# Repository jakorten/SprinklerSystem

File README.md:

# SprinklerSystem
Repository for valve controllers etc.

Here I publish updates to Python and Arduino scripts to create my / your own irrigation system.

## System parts
CinqueValvoleHAT is used to control a pump system.
TinyRelayModule is used to control a larger (230V) relay to switch of the main pump.
DueValvoleZeroBoard is used to control two valves and also features sensors.

## Progress and links

June 2019:
- CinqueValvoleHAT: 5x Valve/Tap Controller board (v1.0 / v1.1) (https://github.com/jakorten/SprinklerSystem/tree/master/CinqueValvoleHAT)
- DueValvoleZeroBoard: 2x Valve/Tap under development, uses a SAMD21 microcontroller and interfaces with a Raspberry Pi Zero (W).
- TinyRelayModule is only a solderboard version for now.

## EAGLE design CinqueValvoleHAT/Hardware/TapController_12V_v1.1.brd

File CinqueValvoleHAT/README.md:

# SprinklerSystem: CinqueValvoleHAT
Repository for valve controllers etc.

## About
Here I publish updates to Python and Arduino scripts to create my / your own irrigation system.

June 2019:
- 5x Tap Controller board (v1.0 / v1.1) (CinqueValvoleHAT)

The CinqueValvoleHAT is used to control up to 5 valves.
- Typical valves have DC motors
- They will switch of when the limit is reached (fully open or fully closed)
- The print was designed to control 12V valves

Other DC motors can also be controlled using this HAT.
We have tested the HAT for 12V and below.

Most parts can handle up to 50V but that is the maximum, of you would
want to control 48V you should change some parts:
- 0.1uF/50V
- 22uF/63V

We use a voltage divider in v1.1 for AOD417, for 12V that would not have been
necessary. The AOD417 protects against wrong polarity.

The input (suggested 5V - 12V) is not connected to the rest of the system only to the
DRV8871 drivers.

Each DRV8871 can handle up to 3.6A (but is limited to about 2A by the 30k resistors) and
has a maximum voltage of 50V (< 45V recommended). In case you want to use the HAT as is
for 48V motors we suggest you make sure your supply only divers 45V or less which should
be more than enough for ball valves. Note: We did not test this so use at your own risk.

We did try to run our 12V ball valves at 7V and although they move slower they will work
just fine.

We used the valves from:
https://nl.aliexpress.com/store/4032047?spm=a2g0o.detail.1000002.2.6d6b58daLNaQAn
(e.g. https://nl.aliexpress.com/item/32896353276.html?spm=a2g0s.9042311.0.0.32b34c4dLBPZam)

## Source
The source lets your Raspberry Pi control the valves via a PCA9685 IC

## Credits

Thanks @Adafruit for not only providing us with the basis idea and HAT layout (https://www.adafruit.com/product/2348).
Their hat works well but we found it got too hot inside the narrow enclosure we used.
Also thanks to @Adafruit for their suggestion to use DRV8871 drivers (they sell separate boards).

Note: we have designed the HAT and software to interoperate with homebridge. We use a second Raspberry Pi that
runs homebridge and will allow to set the valves remotely.

# ToDo: Work in progress
- We have created a HMI system for operation without homebridge
- We still need to integrate this functionality with the current source.
- Other parts of the system will be uploaded as we go.
- We hope to make the system available for purchase using Tindie.

Johan Korten<br>
June 2019

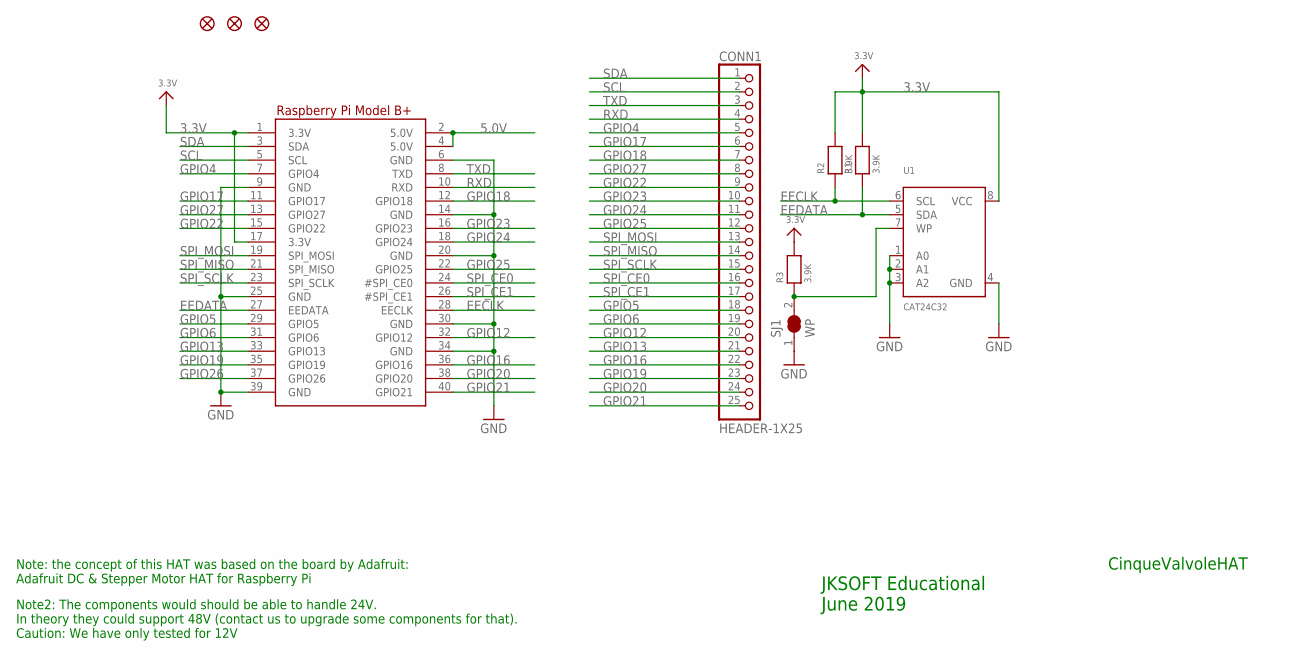
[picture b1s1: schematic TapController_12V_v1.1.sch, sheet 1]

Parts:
CONN1: HEADER-1X25; 1X25_ROUND_70MIL
FID1, FID2, FID3: FIDUCIAL""; FIDUCIAL_1MM
R1, R2, R3: 3.9K; 0805-NO@1
RPI1: RASPBERRYPI_BPLUS_HATSLOTS; PI_HAT_SLOTS
SJ1: WP; SOLDERJUMPER_CLOSEDWIRE
U1: CAT24C32; SOIC8_150MIL

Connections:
3.3V: R1.2, R2.2, R3.2, RPI1.1 (3.3V), RPI1.17 (3.3V), U1.8 (VCC); also elsewhere on the board
5.0V: RPI1.2 (5.0V), RPI1.4 (5.0V)
EECLK: R2.1, RPI1.28 (EECLK), U1.6 (SCL)
EEDATA: R1.1, RPI1.27 (EEDATA), U1.5 (SDA)
GND: RPI1.6 (GND), RPI1.9 (GND), RPI1.14 (GND), RPI1.20 (GND), RPI1.25 (GND), RPI1.30 (GND), RPI1.34 (GND), RPI1.39 (GND), SJ1.1, U1.1 (A0), U1.2 (A1), U1.3 (A2), U1.4 (GND); also elsewhere on the board
GPIO4: CONN1.5, RPI1.7 (GPIO4)
GPIO5: CONN1.18, RPI1.29 (GPIO5)
GPIO6: CONN1.19, RPI1.31 (GPIO6)
GPIO12: CONN1.20, RPI1.32 (GPIO12)
GPIO13: CONN1.21, RPI1.33 (GPIO13)
GPIO16: CONN1.22, RPI1.36 (GPIO16)
GPIO17: CONN1.6, RPI1.11 (GPIO17)
GPIO18: CONN1.7, RPI1.12 (GPIO18)
GPIO19: CONN1.23, RPI1.35 (GPIO19)
GPIO20: CONN1.24, RPI1.38 (GPIO20)
GPIO21: CONN1.25, RPI1.40 (GPIO21)
GPIO22: CONN1.9, RPI1.15 (GPIO22)
GPIO23: CONN1.10, RPI1.16 (GPIO23)
GPIO24: CONN1.11, RPI1.18 (GPIO24)
GPIO25: CONN1.12, RPI1.22 (GPIO25)
GPIO26: RPI1.37 (GPIO26)
GPIO27: CONN1.8, RPI1.13 (GPIO27)
unnamed: R3.1, SJ1.2, U1.7 (WP)
RXD: CONN1.4, RPI1.10 (RXD)
SCL: CONN1.2, RPI1.5 (SCL); also elsewhere on the board
SDA: CONN1.1, RPI1.3 (SDA); also elsewhere on the board
SPI_CE0: CONN1.16, RPI1.24 (#SPI_CE0)
SPI_CE1: CONN1.17, RPI1.26 (#SPI_CE1)
SPI_MISO: CONN1.14, RPI1.21 (SPI_MISO)
SPI_MOSI: CONN1.13, RPI1.19 (SPI_MOSI)
SPI_SCLK: CONN1.15, RPI1.23 (SPI_SCLK)
TXD: CONN1.3, RPI1.8 (TXD)

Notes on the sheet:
JKSOFT Educational June 2019
CinqueValvoleHAT
Note: the concept of this HAT was based on the board by Adafruit: Adafruit DC & Stepper Motor HAT for Raspberry Pi
Note2: The components would should be able to handle 24V. In theory they could support 48V (contact us to upgrade some components for that). Caution: We have only tested for 12V

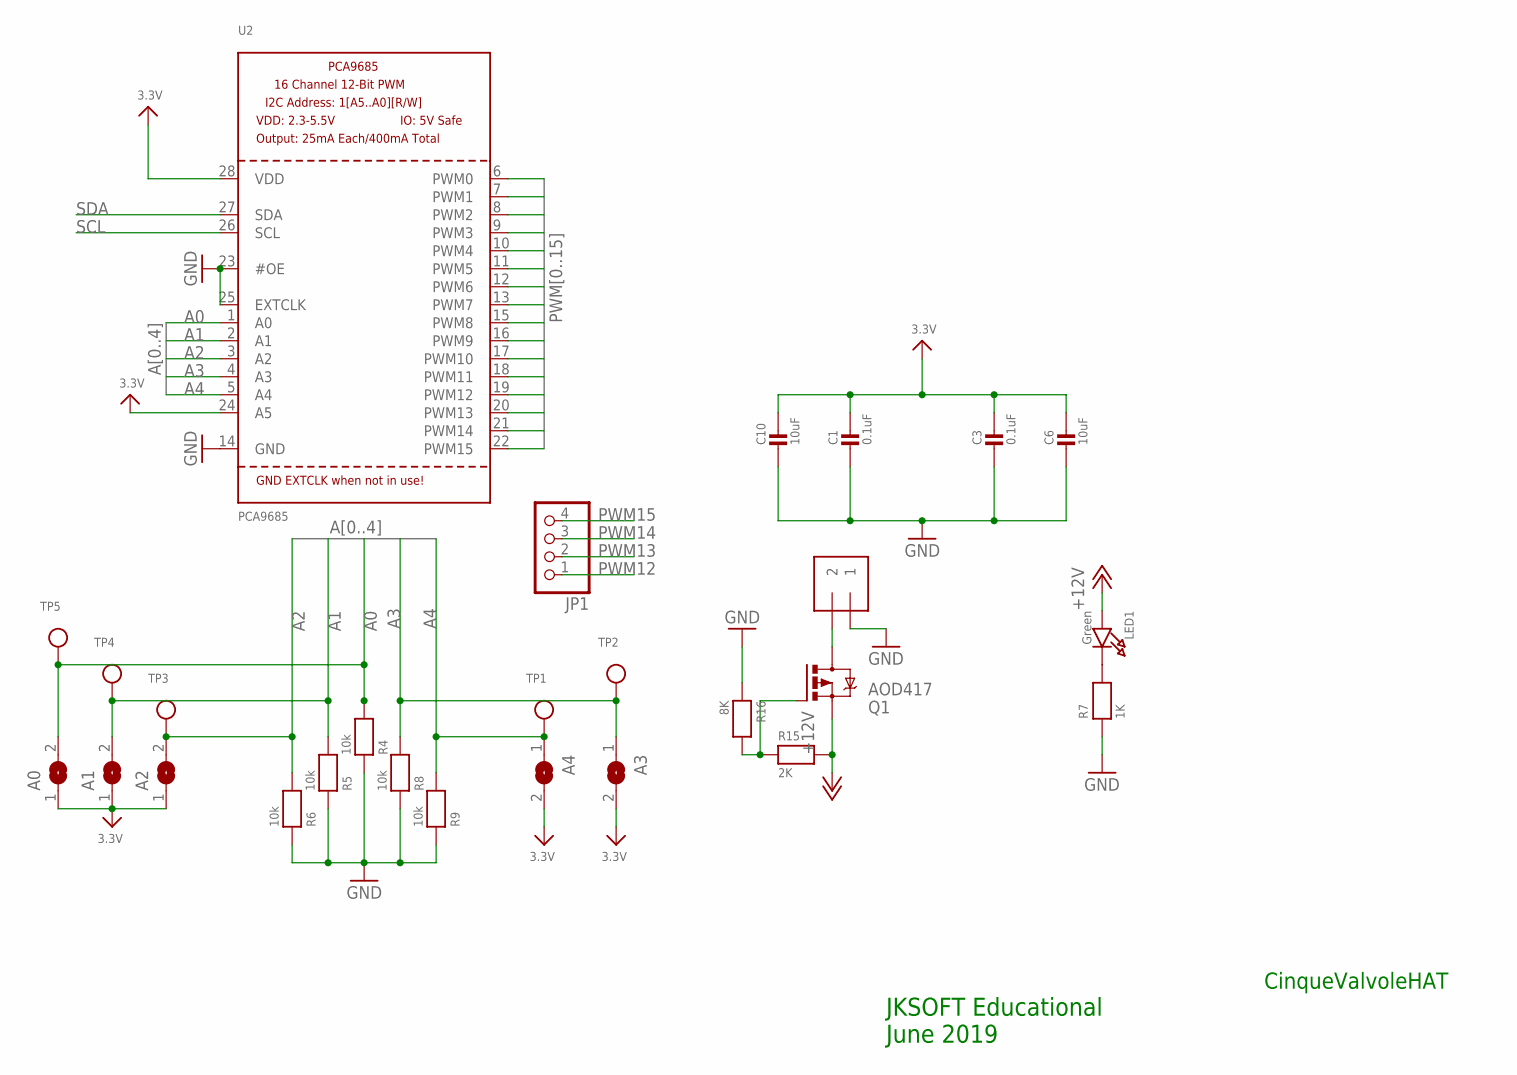
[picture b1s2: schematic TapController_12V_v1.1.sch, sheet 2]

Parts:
A0, A1, A2, A3, A4: SOLDERJUMPERREFLOW_NOPASTE; SOLDERJUMPER_REFLOW_NOPASTE
C1, C3: 0.1uF; 0805-NO
C6, C10: 10uF; 0805-NO
JP1: HEADER-1X476MIL; 1X04_ROUND_76
LED1: Green; CHIPLED_0805_NOOUTLINE
MPOWER: 1X2-3.5MM
Q1: AOD417; D-PAK_TO252AA
R4, R5, R6, R8, R9: 10k; 0805-NO@1
R7: 1K; 0805-NO@1
R15: 2K; 0805-NO@1
R16: 8K; 0805-NO@1
TP1, TP2, TP3, TP4, TP5: TESTPOINTROUND2MM; TESTPOINT_ROUND_2MM
U2: PCA9685; TSSOP28

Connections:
3.3V: A0.1, A1.1, A2.1, A3.2, A4.2, C1.1, C3.1, C6.1, C10.1, U2.24 (A5), U2.28 (VDD); also elsewhere on the board
12V: MPOWER.2, Q1.4 (D)
+12V: LED1.A, Q1.3 (S), R15.2; also elsewhere on the board
A0: A0.2, R4.2, TP5.P$1, U2.1 (A0)
A1: A1.2, R5.2, TP4.P$1, U2.2 (A1)
A2: A2.2, R6.2, TP3.P$1, U2.3 (A2)
A3: A3.1, R8.2, TP2.P$1, U2.4 (A3)
A4: A4.1, R9.2, TP1.P$1, U2.5 (A4)
GND: C1.2, C3.2, C6.2, C10.2, MPOWER.1, R4.1, R5.1, R6.1, R7.1, R8.1, R9.1, R16.1, U2.14 (GND), U2.23 (#OE), U2.25 (EXTCLK); also elsewhere on the board
unnamed: Q1.1 (G), R15.1, R16.2
unnamed: LED1.C, R7.2
PWM0: U2.6 (PWM0); also elsewhere on the board
PWM1: U2.7 (PWM1); also elsewhere on the board
PWM2: U2.8 (PWM2); also elsewhere on the board
PWM3: U2.9 (PWM3); also elsewhere on the board
PWM4: U2.10 (PWM4); also elsewhere on the board
PWM5: U2.11 (PWM5); also elsewhere on the board
PWM6: U2.12 (PWM6); also elsewhere on the board
PWM7: U2.13 (PWM7); also elsewhere on the board
PWM8: U2.15 (PWM8); also elsewhere on the board
PWM9: U2.16 (PWM9); also elsewhere on the board
PWM10: U2.17 (PWM10)
PWM11: U2.18 (PWM11)
PWM12: JP1.1, U2.19 (PWM12)
PWM13: JP1.2, U2.20 (PWM13)
PWM14: JP1.3, U2.21 (PWM14)
PWM15: JP1.4, U2.22 (PWM15)
SCL: U2.26 (SCL); also elsewhere on the board
SDA: U2.27 (SDA); also elsewhere on the board

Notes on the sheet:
JKSOFT Educational June 2019
CinqueValvoleHAT

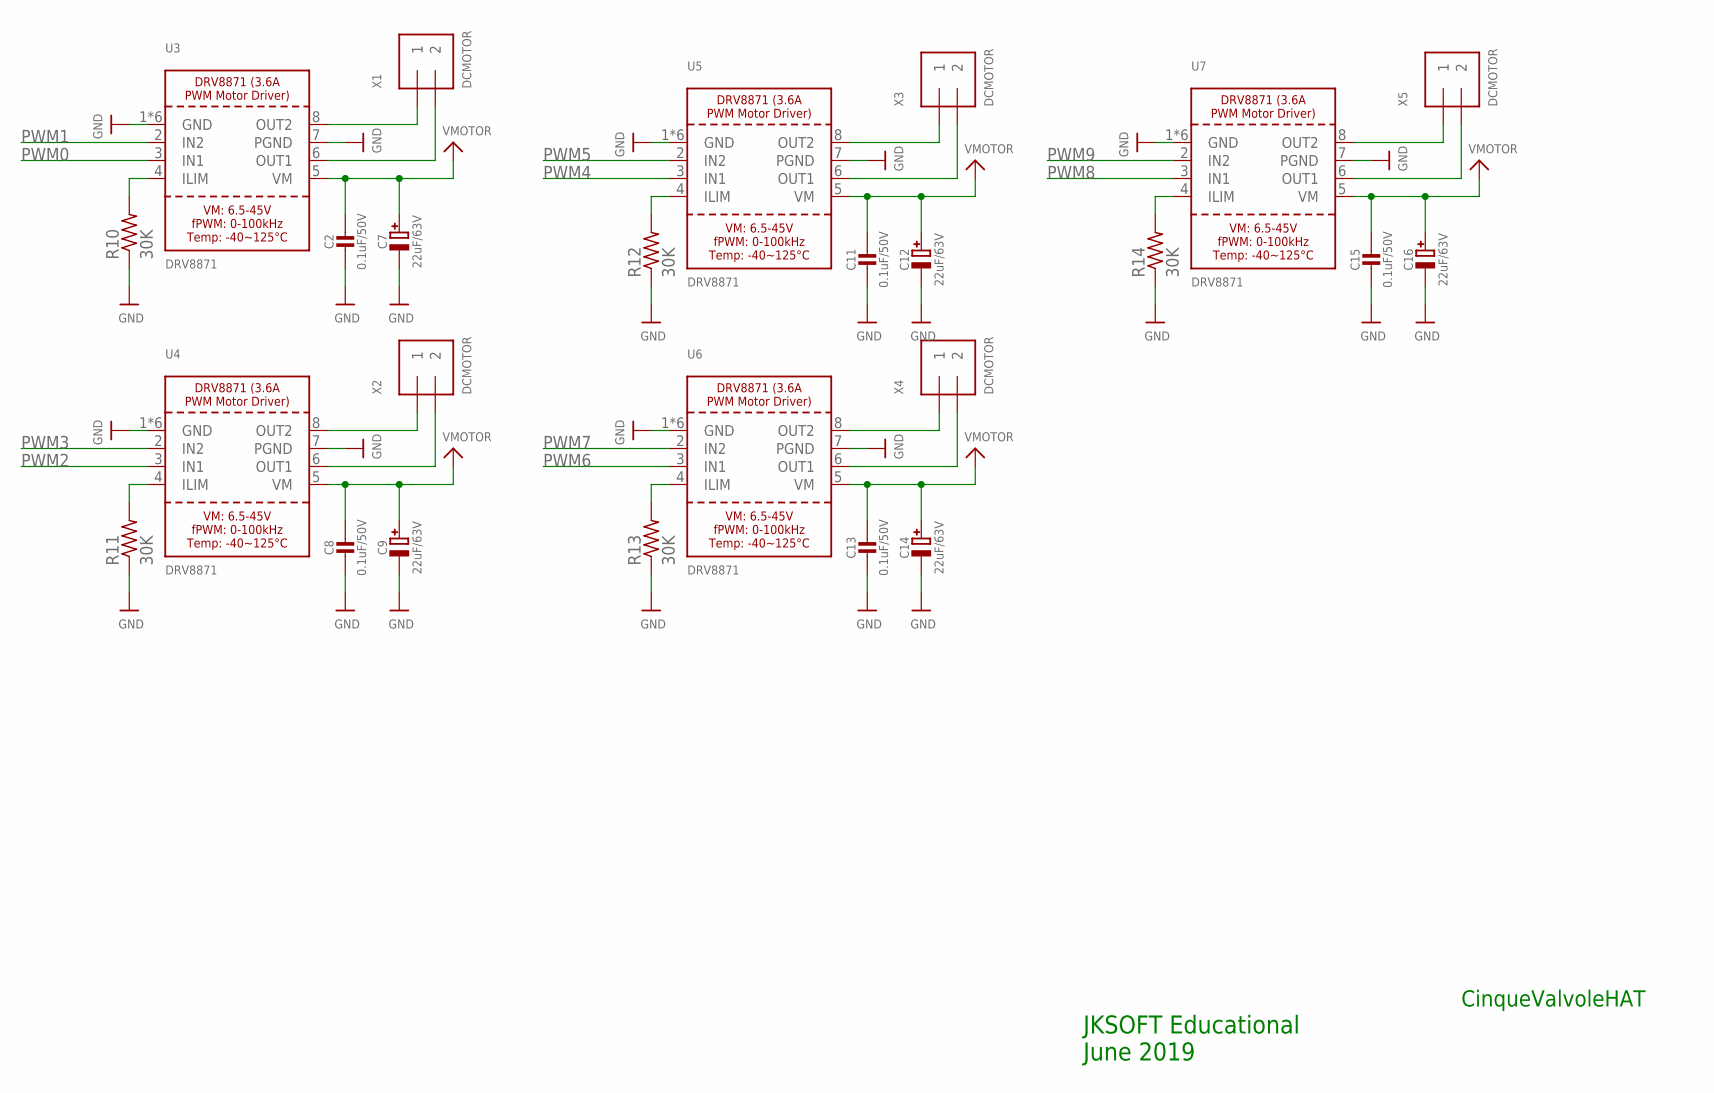
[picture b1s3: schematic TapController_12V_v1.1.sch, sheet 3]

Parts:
C2, C8, C11, C13, C15: 0.1uF/50V; 0805-NO
C7, C9, C12, C14, C16: 22uF/63V; PANASONIC_D
R10, R11, R12, R13, R14: 30K; R0805W
U3, U4, U5, U6, U7: DRV8871; HSOP8
X1, X2, X3, X4, X5: DCMOTOR; TERMBLOCK_1X2-3.5MM

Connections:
+12V: C2.1, C7.+, C8.1, C9.+, C11.1, C12.+, C13.1, C14.+, C15.1, C16.+, U3.5 (VM), U4.5 (VM), U5.5 (VM), U6.5 (VM), U7.5 (VM); also elsewhere on the board
GND: C2.2, C7.-, C8.2, C9.-, C11.2, C12.-, C13.2, C14.-, C15.2, C16.-, R10.1, R11.1, R12.1, R13.1, R14.1, U3.1 (GND), U3.7 (PGND), U3.GND, U3.P$1 (GND), U3.P$2 (GND), U3.P$3 (GND), U3.P$4 (GND), U4.1 (GND), U4.7 (PGND), U4.GND, U4.P$1 (GND), U4.P$2 (GND), U4.P$3 (GND), U4.P$4 (GND), U5.1 (GND), U5.7 (PGND), U5.GND, U5.P$1 (GND), U5.P$2 (GND), U5.P$3 (GND), U5.P$4 (GND), U6.1 (GND), U6.7 (PGND), U6.GND, U6.P$1 (GND), U6.P$2 (GND), U6.P$3 (GND), U6.P$4 (GND), U7.1 (GND), U7.7 (PGND), U7.GND, U7.P$1 (GND), U7.P$2 (GND), U7.P$3 (GND), U7.P$4 (GND); also elsewhere on the board
unnamed: R10.2, U3.4 (ILIM)
unnamed: R11.2, U4.4 (ILIM)
unnamed: R12.2, U5.4 (ILIM)
unnamed: R13.2, U6.4 (ILIM)
unnamed: R14.2, U7.4 (ILIM)
OUT1: U3.6 (OUT1), X1.2
OUT2: U3.8 (OUT2), X1.1
OUT3: U4.8 (OUT2), X2.1
OUT4: U4.6 (OUT1), X2.2
OUT5: U5.8 (OUT2), X3.1
OUT6: U5.6 (OUT1), X3.2
OUT7: U6.8 (OUT2), X4.1
OUT8: U6.6 (OUT1), X4.2
OUT9: U7.8 (OUT2), X5.1
OUT10: U7.6 (OUT1), X5.2
PWM0: U3.3 (IN1); also elsewhere on the board
PWM1: U3.2 (IN2); also elsewhere on the board
PWM2: U4.3 (IN1); also elsewhere on the board
PWM3: U4.2 (IN2); also elsewhere on the board
PWM4: U5.3 (IN1); also elsewhere on the board
PWM5: U5.2 (IN2); also elsewhere on the board
PWM6: U6.3 (IN1); also elsewhere on the board
PWM7: U6.2 (IN2); also elsewhere on the board
PWM8: U7.3 (IN1); also elsewhere on the board
PWM9: U7.2 (IN2); also elsewhere on the board

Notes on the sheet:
JKSOFT Educational June 2019
CinqueValvoleHAT

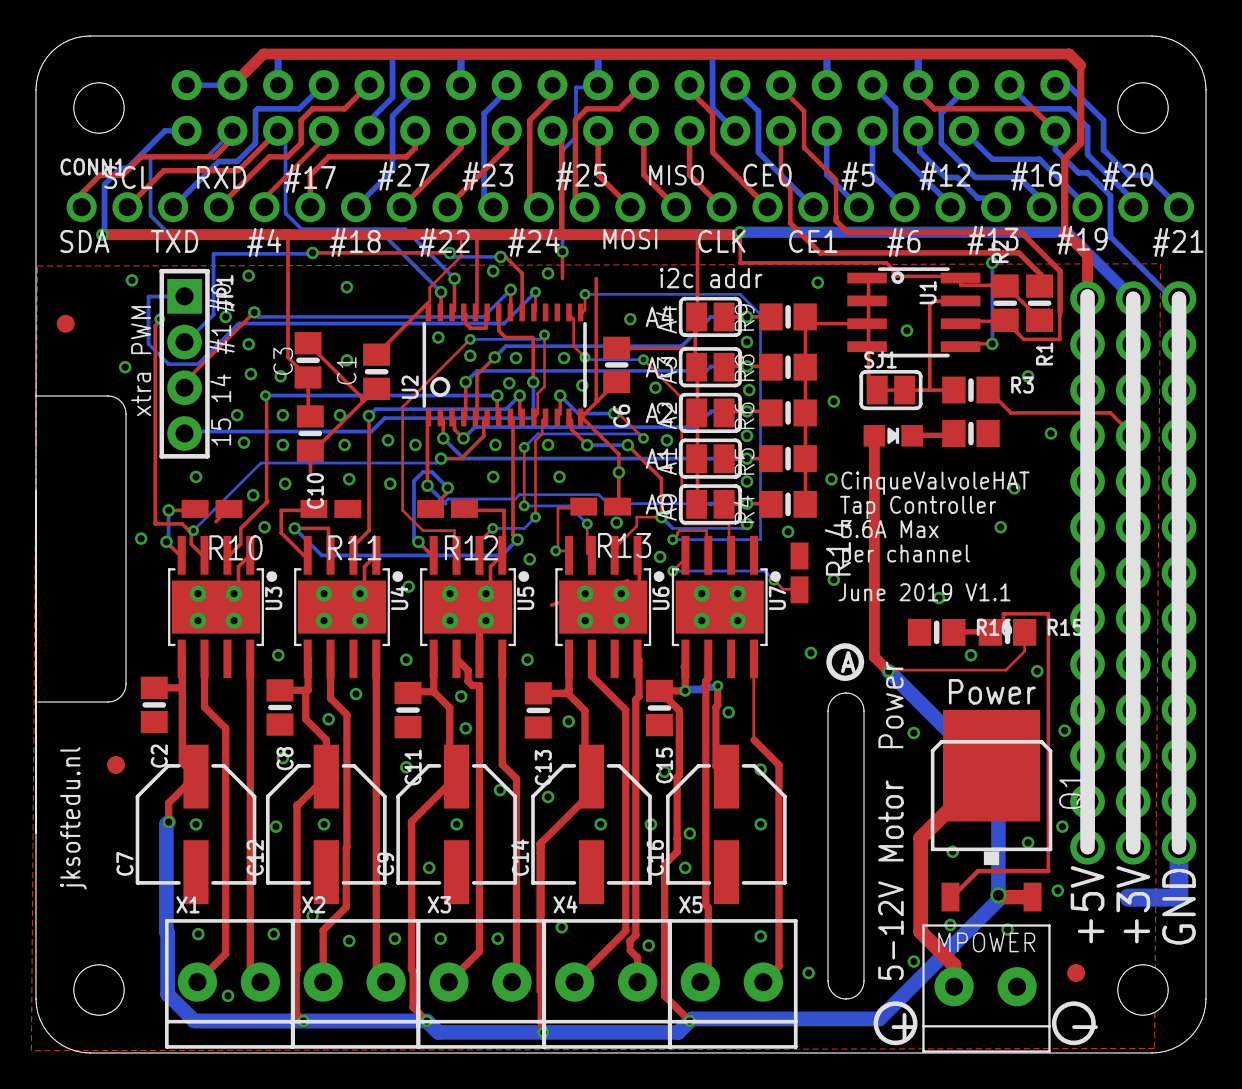
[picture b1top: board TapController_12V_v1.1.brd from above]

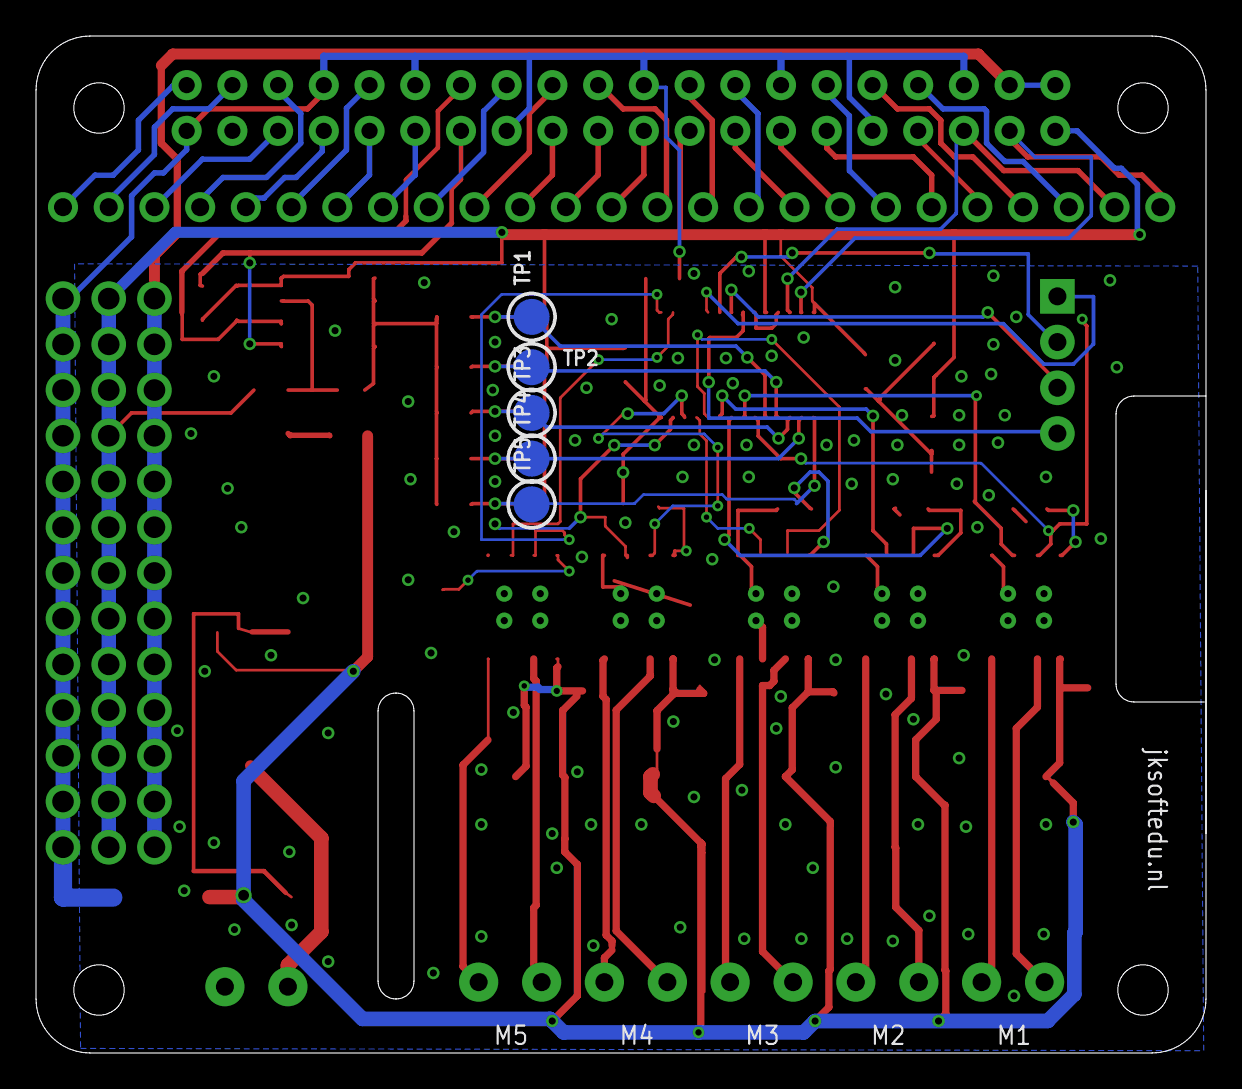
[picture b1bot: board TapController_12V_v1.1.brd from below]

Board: 2 copper layers, 65.0 x 56.5 mm, 63 parts (5 on the bottom side), 69 nets.

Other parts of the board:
U$6: PCBFEAT-REV-040

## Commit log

2019-06-17 Initial commit
    Updates
2019-06-17 Updates
    Updates
2019-06-17 Updated README
    Updated README
2019-06-20 update debug print
    update debug print

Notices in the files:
parts and their libraries:
microbuilder: This work is placed in the public domain, and may be freely used for commercial and non-commercial work with the following conditions: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
